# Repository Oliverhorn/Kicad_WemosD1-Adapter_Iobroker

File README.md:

# Kicad_WemosD1 Adapter_Iobroker

TO DO für Revision 2:

 1. DSS18B20_GPIO (J1.Pin9) muss noch mit D2(GPIO4) am WEMOS D1 verbunden werden (Leitung fehlt.)
 2. J1 ersetzen gegen JST Buchse, o.ä.. Pinheader sind ungeeignet. Leitungen ziehen sich selbst wieder von Pinheader herunter. Keine Verriegelung!
 3. Outline anpassen an Gehäuse

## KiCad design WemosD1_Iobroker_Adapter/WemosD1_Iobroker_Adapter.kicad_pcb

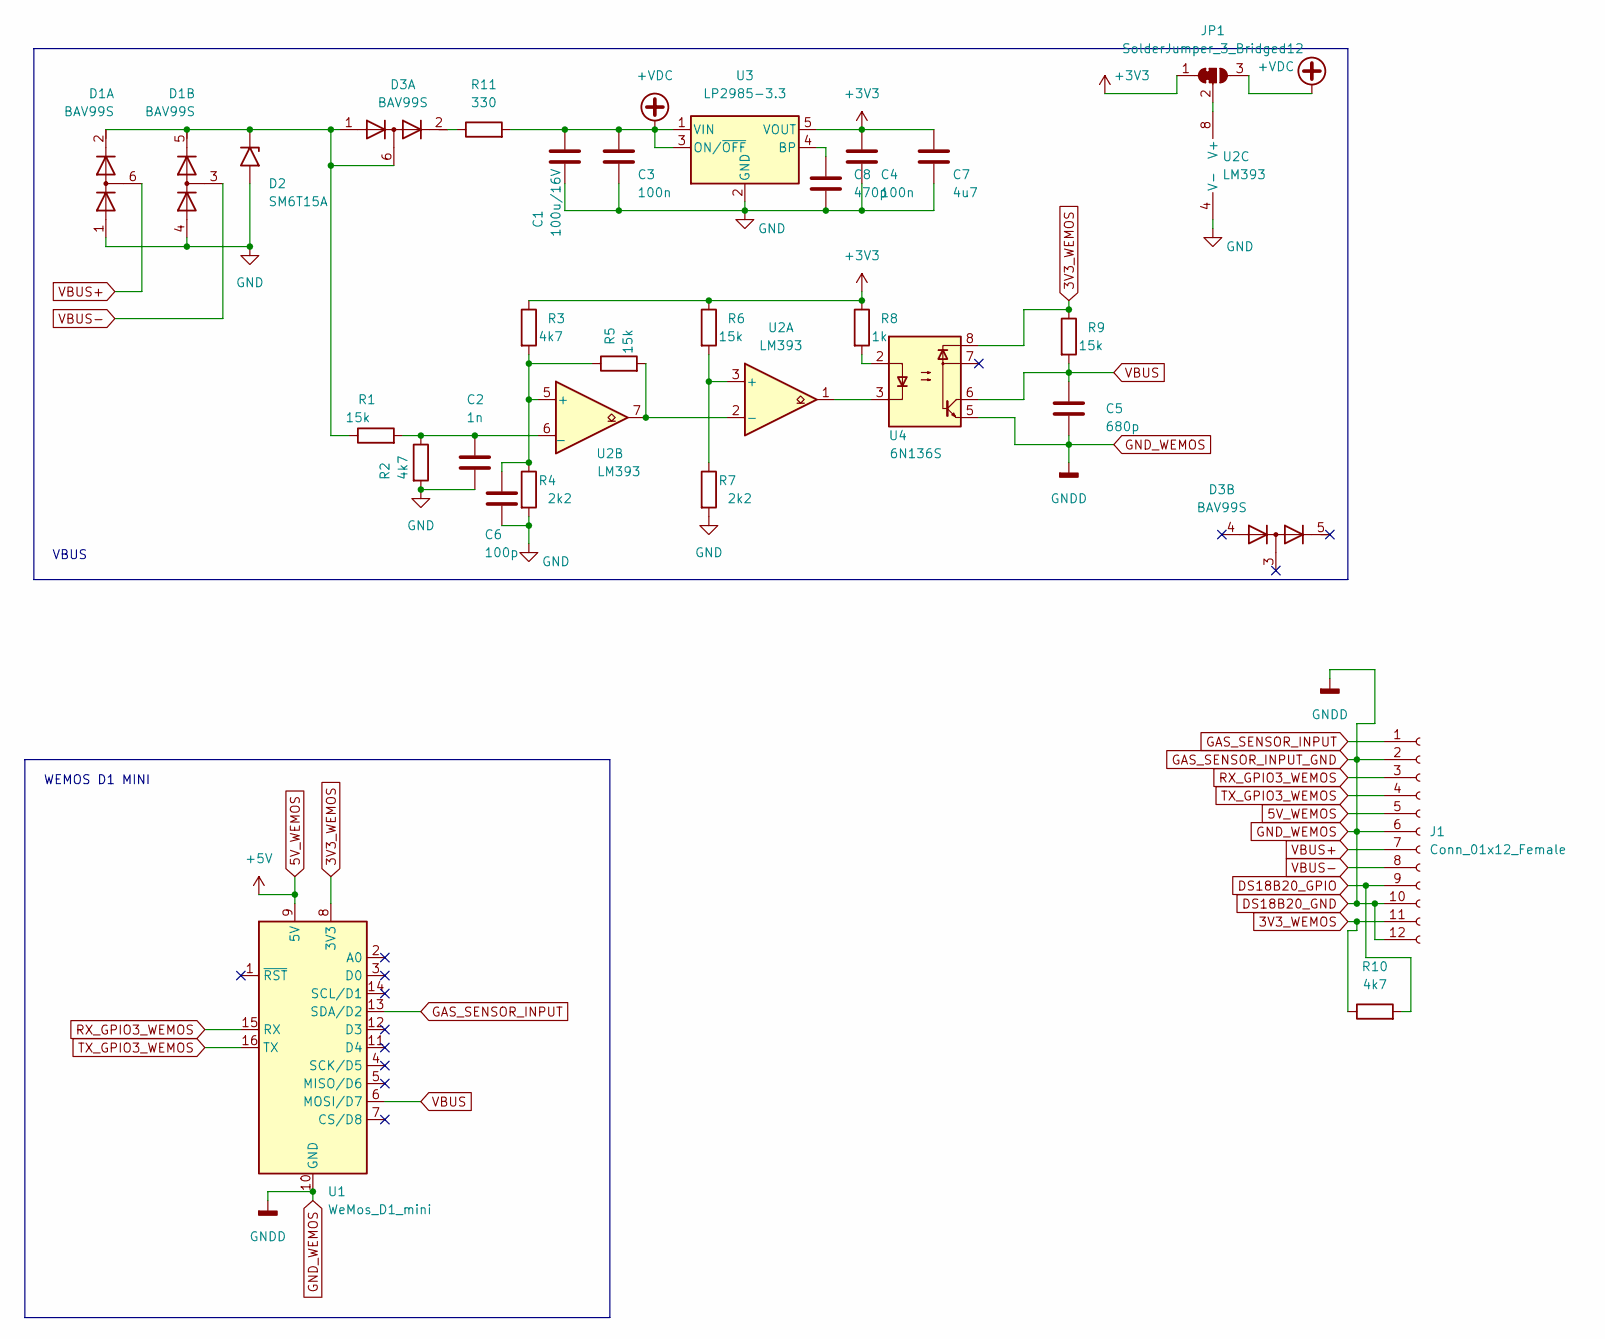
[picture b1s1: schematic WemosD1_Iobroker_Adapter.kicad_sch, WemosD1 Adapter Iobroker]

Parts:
C1: 100u/16V; CP_Elec_6.3x5.4_Nichicon; LCSC Part # C111600
C2: 1n; C_0402_1005Metric; LCSC Part # C1523
C3, C4: 100n; C_0402_1005Metric; LCSC Part # C307331
C5: 680p; C_0603_1608Metric; LCSC Part # C1630
C6: 100p; C_0402_1005Metric; LCSC Part # C1546
C7: 4u7; C_0402_1005Metric; LCSC Part # C307331
C8: 470p; C_0402_1005Metric; LCSC Part # C1537
D1, D3: BAV99S; SOT-363_SC-70-6; LCSC Part # C68987
D2: SM6T15A; D_SMB; LCSC Part # C1974359
J1: Conn_01x12_Female; PinHeader_2x06_P2.54mm_Horizontal; LCSC Part # C492434
JP1: SolderJumper_3_Bridged12; SolderJumper-3_P1.3mm_Bridged12_RoundedPad1.0x1.5mm_NumberL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
R1, R5, R6, R9: 15k; R_0402_1005Metric; LCSC Part # C25756
R2, R3: 4k7; R_0402_1005Metric; LCSC Part # C25900
R4, R7: 2k2; R_0402_1005Metric; LCSC Part # C25879
R8: 1k; R_0402_1005Metric; LCSC Part # C11702
R10: 4k7; R_0402_1005Metric; MPN C25900
R11: 330; R_0402_1005Metric; LCSC Part # C25104
U1: WeMos_D1_mini; WEMOS_D1_mini_light
U2: LM393; SOIC-8_3.9x4.9mm_P1.27mm; LCSC Part # C7955
U3: LP2985-3.3; SOT-23-5; LCSC Part # C95414
U4: 6N136S; SMDIP-8_W9.53mm; LCSC Part # C118756

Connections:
3V3_WEMOS: J1.11, R9.1, R10.1, U1.8 (3V3), U4.8
5V_WEMOS: J1.5, U1.9 (5V)
+3V3: C4.1, C7.1, JP1.1 (A), R3.1, R6.1, R8.1, U3.5 (VOUT)
+VDC: C1.1, C3.1, JP1.3 (B), R11.2, U3.1 (VIN), U3.3 (ON/~OFF)
DS18B20_GND: C5.2, J1.2, J1.6, J1.10, J1.12, U1.10 (GND), U4.5
DS18B20_GPIO: J1.9, R10.2
GAS_SENSOR_INPUT: J1.1, U1.13 (SDA/D2)
GND: C1.2, C2.2, C3.2, C4.2, C6.2, C7.2, C8.2, D1.1 (A1), D1.4 (A3), D2.2 (A2), R2.2, R4.2, R7.2, U2.4 (V-), U3.2 (GND)
unnamed: C2.1, R1.2, R2.1, U2.6 (_)
unnamed: C6.1, R3.2, R4.1, R5.1, U2.5 (+)
unnamed: C8.1, U3.4 (BP)
unnamed: D1.2 (K2), D1.5 (K4), D2.1 (A1), D3.1 (A1), D3.6 (K3A4), R1.1
unnamed: D3.2 (K2), R11.1
unnamed: JP1.2 (C), U2.8 (V+)
unnamed: R5.2, U2.2 (-), U2.7
unnamed: R6.2, R7.1, U2.3 (+)
unnamed: R8.2, U4.2
unnamed: U2.1, U4.3
RX_GPIO3_WEMOS: J1.3, U1.15 (RX)
TX_GPIO3_WEMOS: J1.4, U1.16 (TX)
VBUS: C5.1, R9.2, U1.6 (MOSI/D7), U4.6
VBUS+: D1.6 (K3A4), J1.7
VBUS-: D1.3 (K1A2), J1.8

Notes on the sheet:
VBUS
WEMOS D1 MINI

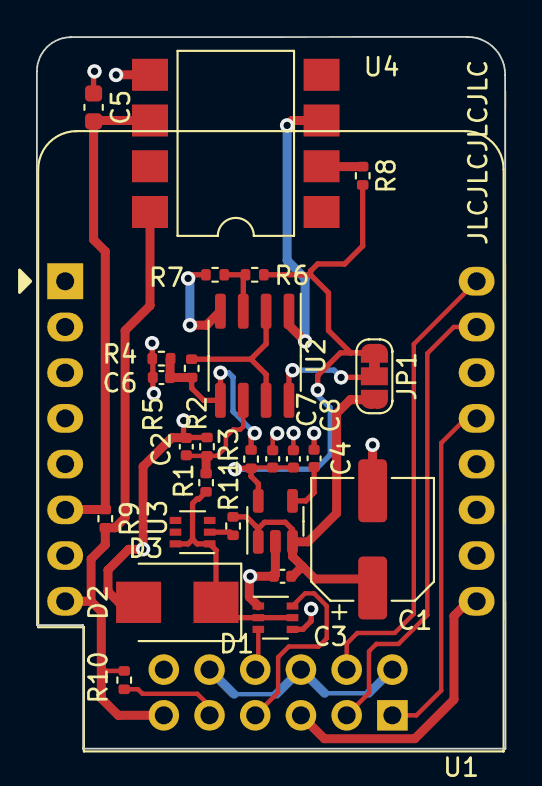
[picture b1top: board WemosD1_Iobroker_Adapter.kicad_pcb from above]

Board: 2 copper layers, 26.0 x 39.5 mm, 28 parts (1 on the bottom side), 23 nets.

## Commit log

2022-09-12 initial
2022-09-28 Update README.md
    Updates für potentielle Rev2
